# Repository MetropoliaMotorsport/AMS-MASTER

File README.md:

Changes for next year:
Labels on other side
Remove unused connectors
Add connection for temperature measurement of DCDC

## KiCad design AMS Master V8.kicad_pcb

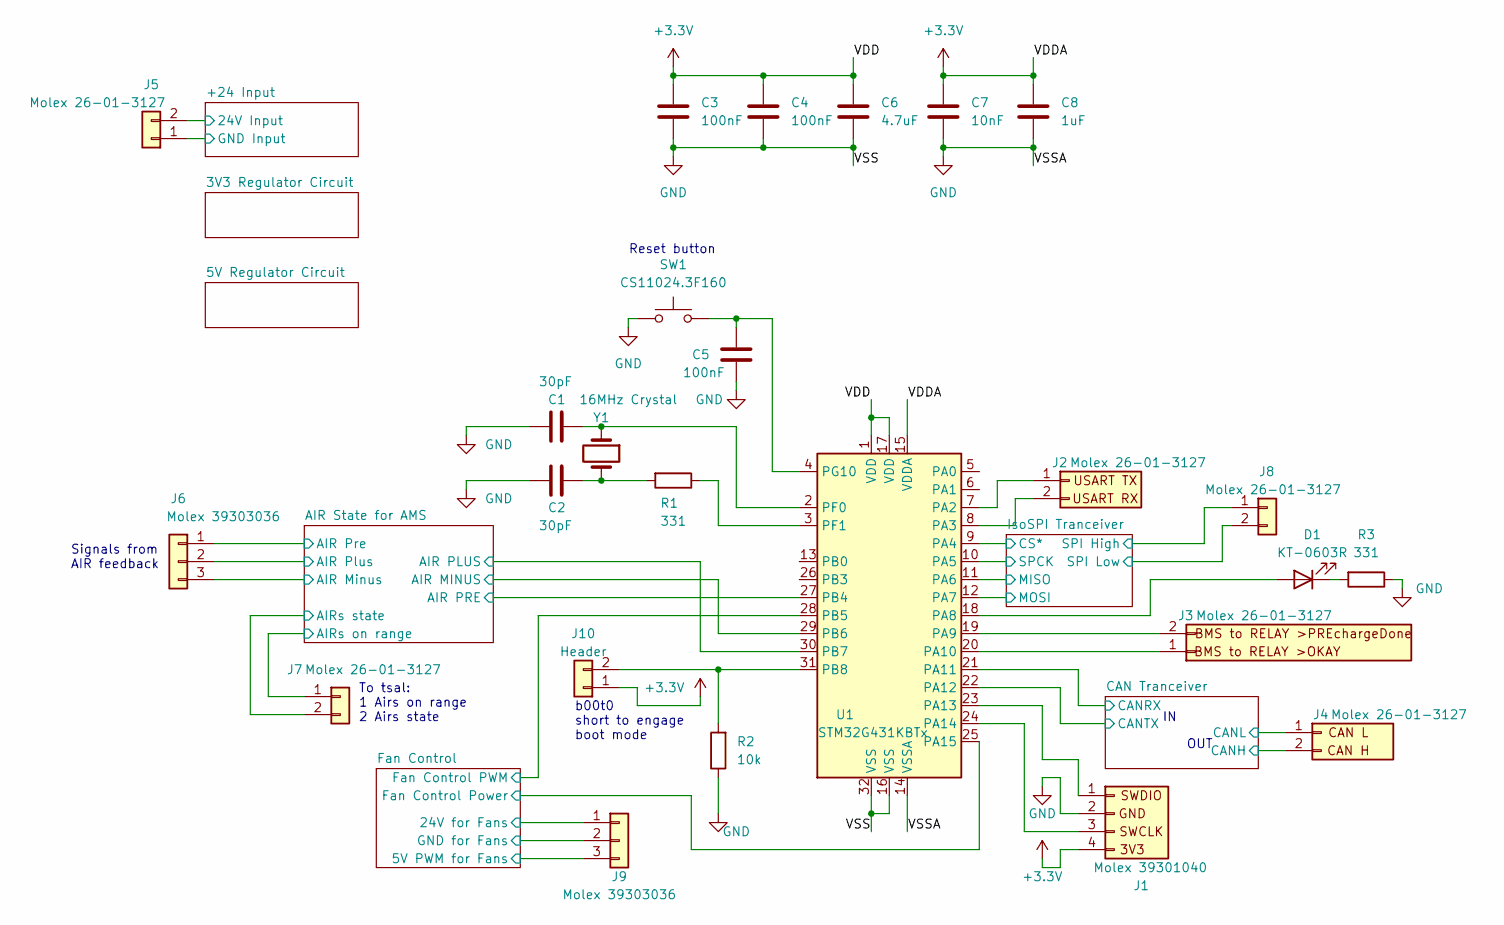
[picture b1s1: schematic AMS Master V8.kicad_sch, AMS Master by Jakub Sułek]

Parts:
C1, C2: 30pF; C_0805_2012Metric_Pad1.18x1.45mm_HandSolder
C3, C4: 100nF; C_0603_1608Metric_Pad1.08x0.95mm_HandSolder
C5: 100nF; C_0805_2012Metric_Pad1.18x1.45mm_HandSolder
C6: 4.7uF; C_0603_1608Metric_Pad1.08x0.95mm_HandSolder
C7: 10nF; C_0603_1608Metric_Pad1.08x0.95mm_HandSolder
C8: 1uF; C_0603_1608Metric_Pad1.08x0.95mm_HandSolder
D1: KT-0603R; LED_0603_1608Metric_Pad1.05x0.95mm_HandSolder
J1: Molex 39301040; Molex_Mini-Fit_Jr_5569-04A2_2x02_P4.20mm_Horizontal
J2, J3, J4, J5, J7, J8: Molex 26-01-3127; Molex_Mini-Fit_Jr_5569-02A2_2x01_P4.20mm_Horizontal
J6, J9: Molex 39303036; Molex_Mini-Fit_Jr_5569-03A4_1x03_P4.20mm_Horizontal
J10: Header; PinHeader_1x02_P2.54mm_Vertical
R1, R3: 331; R_0603_1608Metric_Pad0.98x0.95mm_HandSolder
R2: 10k; R_0805_2012Metric_Pad1.20x1.40mm_HandSolder
SW1: CS11024.3F160; SW_Push_1P1T_NO_6x6mm_H9.5mm
U1: STM32G431KBTx; LQFP-32_7x7mm_P0.8mm
Y1: 16MHz Crystal; Crystal_SMD_HC49-SD

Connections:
+VDC: J5.2; also elsewhere on the board
/AIR State for AMS/AIR MINUS: U1.29 (PB6); also elsewhere on the board
/AIR State for AMS/AIR Minus: J6.3; also elsewhere on the board
/AIR State for AMS/AIR PLUS: U1.30 (PB7); also elsewhere on the board
/AIR State for AMS/AIR PRE: U1.27 (PB4); also elsewhere on the board
/AIR State for AMS/AIR Plus: J6.2; also elsewhere on the board
/AIR State for AMS/AIR Pre: J6.1; also elsewhere on the board
/AIR State for AMS/AIRs on range: J7.1; also elsewhere on the board
/AIR State for AMS/AIRs state: J7.2; also elsewhere on the board
/CAN Tranceiver/CANH: J4.2; also elsewhere on the board
/CAN Tranceiver/CANL: J4.1; also elsewhere on the board
/CAN Tranceiver/CANRX: U1.21 (PA11); also elsewhere on the board
/CAN Tranceiver/CANTX: U1.22 (PA12); also elsewhere on the board
/Fan Control/5V PWM for Fans: J9.3, U1.28 (PB5)
/Fan Control/24V for Fans: J9.1; also elsewhere on the board
/Fan Control/Fan Control Power: U1.25 (PA15); also elsewhere on the board
/IsoSPI Tranceiver/CS*: U1.9 (PA4); also elsewhere on the board
/IsoSPI Tranceiver/MISO: U1.11 (PA6); also elsewhere on the board
/IsoSPI Tranceiver/MOSI: U1.12 (PA7); also elsewhere on the board
/IsoSPI Tranceiver/SPCK: U1.10 (PA5); also elsewhere on the board
/IsoSPI Tranceiver/SPI High: J8.1; also elsewhere on the board
/IsoSPI Tranceiver/SPI Low: J8.2; also elsewhere on the board
unnamed: C2.1, R1.2, Y1.2
unnamed: D1.2 (A), U1.18 (PA8)
unnamed: D1.1 (K), R3.2
unnamed: J1.1, U1.23 (PA13)
unnamed: J1.3, U1.24 (PA14)
unnamed: J2.1, U1.7 (PA2)
unnamed: J2.2, U1.8 (PA3)
unnamed: J3.1, U1.20 (PA10)
unnamed: J3.2, U1.19 (PA9)
unnamed: J10.2, R2.2, U1.31 (PB8)
unnamed: C1.1, U1.2 (PF0), Y1.1
unnamed: R1.1, U1.3 (PF1)
unnamed: C5.1, SW1.2, U1.4 (PG10)

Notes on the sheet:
OUT
Reset button
To tsal: 1 Airs on range 2 Airs state
b00t0 short to engage boot mode
Signals from AIR feedback

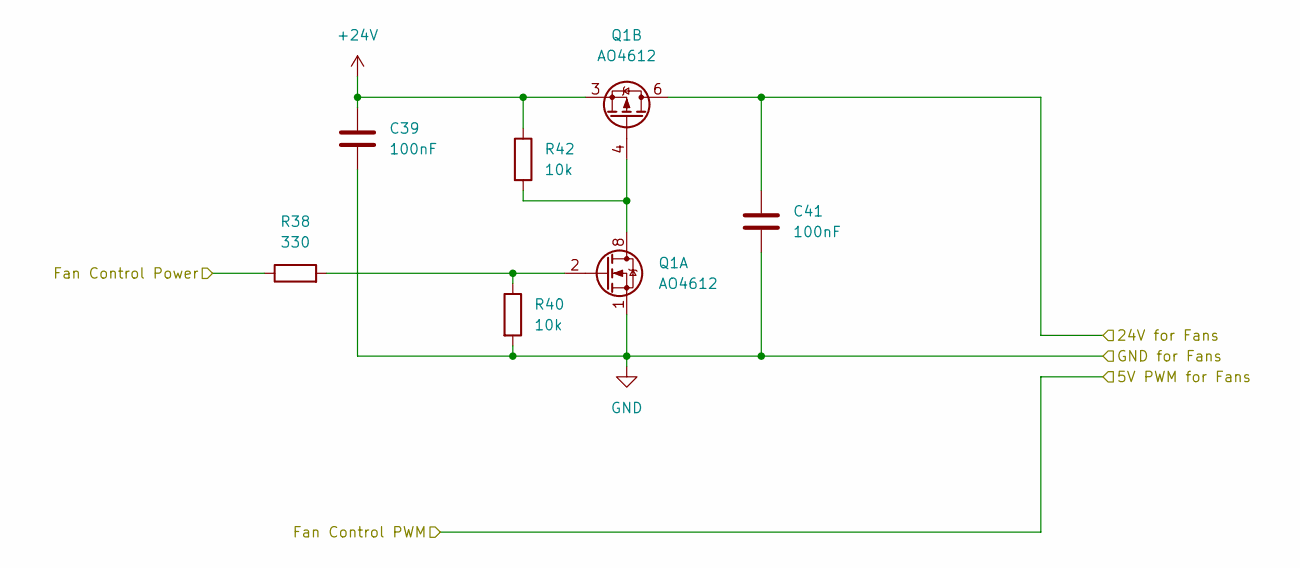
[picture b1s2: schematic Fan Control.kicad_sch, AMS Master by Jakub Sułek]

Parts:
C39, C41: 100nF; C_0805_2012Metric_Pad1.18x1.45mm_HandSolder
Q1: AO4612; SOIC-8_3.9x4.9mm_P1.27mm
R38: 330; R_0805_2012Metric_Pad1.20x1.40mm_HandSolder
R40, R42: 10k; R_0805_2012Metric_Pad1.20x1.40mm_HandSolder

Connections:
+24V: C39.1, Q1.3 (1), R42.1; also elsewhere on the board
/Fan Control/24V for Fans: C41.1, Q1.5 (D), Q1.6 (D); also elsewhere on the board
/Fan Control/Fan Control Power: R38.1; also elsewhere on the board
unnamed: Q1.2 (G), R38.2, R40.1
unnamed: Q1.4 (G), Q1.7 (D), Q1.8 (D), R42.2

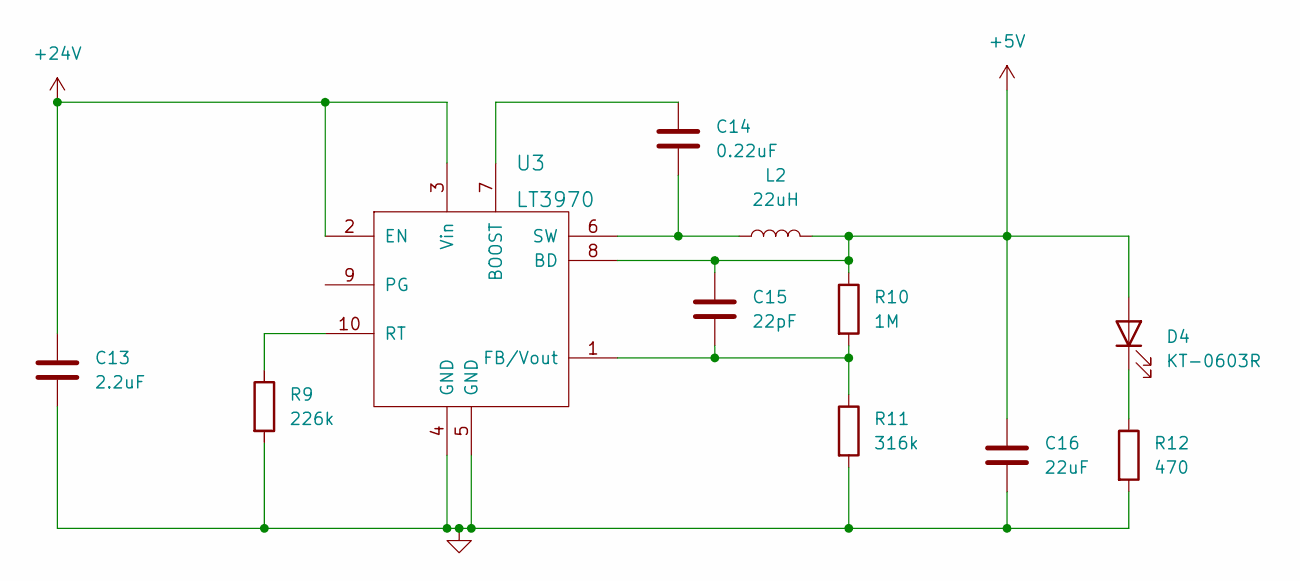
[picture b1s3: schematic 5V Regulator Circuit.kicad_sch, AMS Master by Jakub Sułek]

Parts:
C13: 2.2uF; C_0805_2012Metric_Pad1.18x1.45mm_HandSolder
C14: 0.22uF; C_0805_2012Metric_Pad1.18x1.45mm_HandSolder
C15: 22pF; C_0805_2012Metric_Pad1.18x1.45mm_HandSolder
C16: 22uF; C_0805_2012Metric_Pad1.18x1.45mm_HandSolder
D4: KT-0603R; LED_0603_1608Metric_Pad1.05x0.95mm_HandSolder
L2: 22uH; SLF7045T
R9: 226k; R_0805_2012Metric_Pad1.20x1.40mm_HandSolder
R10: 1M; R_0805_2012Metric_Pad1.20x1.40mm_HandSolder
R11: 316k; R_0805_2012Metric_Pad1.20x1.40mm_HandSolder
R12: 470; R_0805_2012Metric_Pad1.20x1.40mm_HandSolder
U3: LT3970

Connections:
+5V: C15.1, C16.1, D4.2 (A), L2.2, R10.1, U3.8 (BD); also elsewhere on the board
+24V: C13.1, U3.2 (EN), U3.3 (Vin); also elsewhere on the board
unnamed: D4.1 (K), R12.1
unnamed: C14.1, U3.7 (BOOST)
unnamed: C15.2, R10.2, R11.1, U3.1 (FB/Vout)
unnamed: R9.1, U3.10 (RT)
unnamed: C14.2, L2.1, U3.6 (SW)

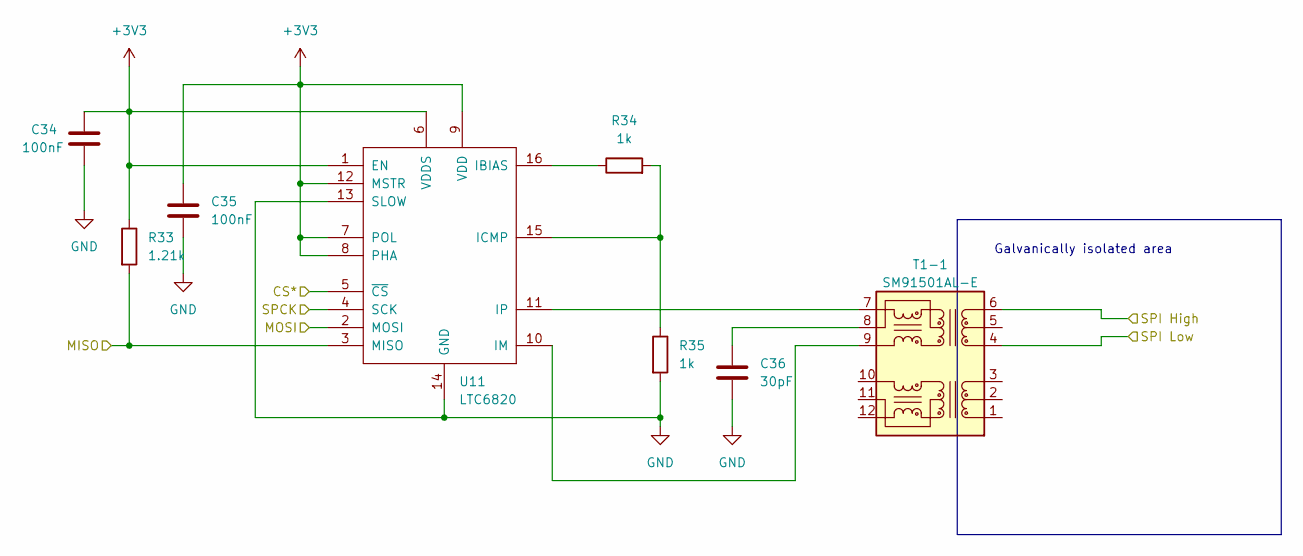
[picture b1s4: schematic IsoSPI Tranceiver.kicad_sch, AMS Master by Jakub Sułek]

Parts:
C34, C35: 100nF; C_0805_2012Metric_Pad1.18x1.45mm_HandSolder
C36: 30pF; C_0805_2012Metric_Pad1.18x1.45mm_HandSolder
R33: 1.21k; R_0805_2012Metric_Pad1.20x1.40mm_HandSolder
R34, R35: 1k; R_0805_2012Metric_Pad1.20x1.40mm_HandSolder
T1-1: SM91501AL-E
U11: LTC6820; ltc6820

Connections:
/IsoSPI Tranceiver/CS*: U11.5 (~CS); also elsewhere on the board
/IsoSPI Tranceiver/MISO: R33.2, U11.3 (MISO); also elsewhere on the board
/IsoSPI Tranceiver/MOSI: U11.2 (MOSI); also elsewhere on the board
/IsoSPI Tranceiver/SPCK: U11.4 (SCK); also elsewhere on the board
/IsoSPI Tranceiver/SPI High: T1-1.6; also elsewhere on the board
/IsoSPI Tranceiver/SPI Low: T1-1.4; also elsewhere on the board
unnamed: C36.1, T1-1.8
unnamed: R34.1, U11.16 (IBIAS)
unnamed: R34.2, R35.1, U11.15 (ICMP)
unnamed: T1-1.9, U11.10 (IM)
unnamed: T1-1.7, U11.11 (IP)

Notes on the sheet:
Galvanically isolated area

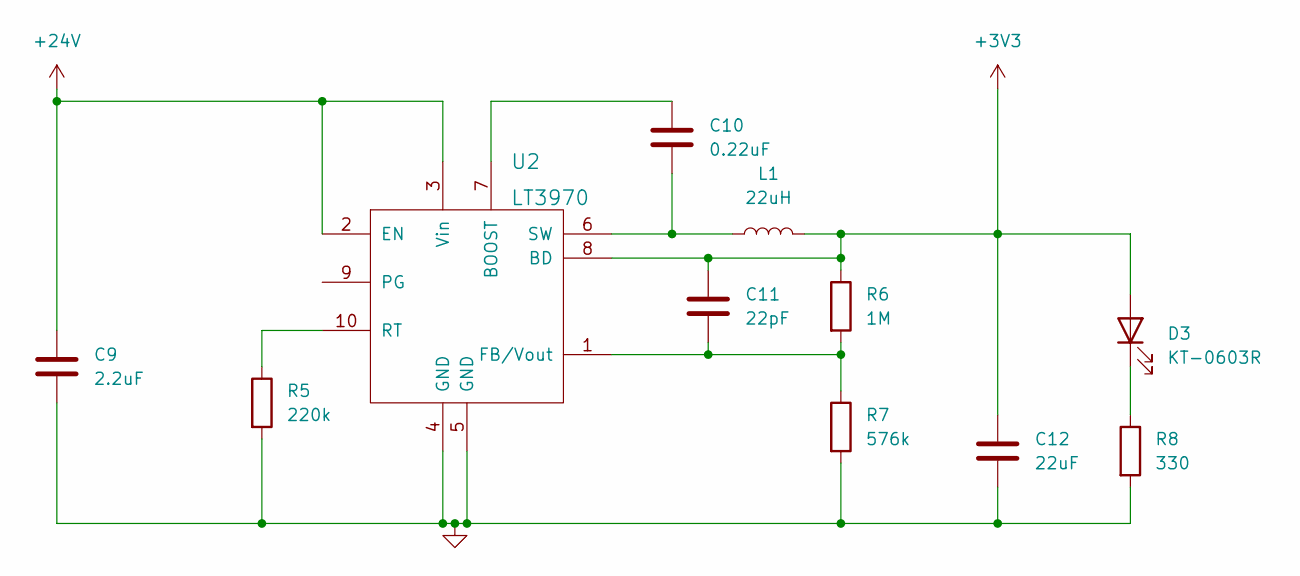
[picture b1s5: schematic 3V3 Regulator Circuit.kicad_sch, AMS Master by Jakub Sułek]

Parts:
C9: 2.2uF; C_0805_2012Metric_Pad1.18x1.45mm_HandSolder
C10: 0.22uF; C_0805_2012Metric_Pad1.18x1.45mm_HandSolder
C11: 22pF; C_0805_2012Metric_Pad1.18x1.45mm_HandSolder
C12: 22uF; C_0805_2012Metric_Pad1.18x1.45mm_HandSolder
D3: KT-0603R; LED_0603_1608Metric_Pad1.05x0.95mm_HandSolder
L1: 22uH; SLF7045T
R5: 220k; R_0805_2012Metric_Pad1.20x1.40mm_HandSolder
R6: 1M; R_0805_2012Metric_Pad1.20x1.40mm_HandSolder
R7: 576k; R_0805_2012Metric_Pad1.20x1.40mm_HandSolder
R8: 330; R_0805_2012Metric_Pad1.20x1.40mm_HandSolder
U2: LT3970

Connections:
+24V: C9.1, U2.2 (EN), U2.3 (Vin); also elsewhere on the board
unnamed: D3.1 (K), R8.1
unnamed: C10.1, U2.7 (BOOST)
unnamed: C11.2, R6.2, R7.1, U2.1 (FB/Vout)
unnamed: R5.1, U2.10 (RT)
unnamed: C10.2, L1.1, U2.6 (SW)

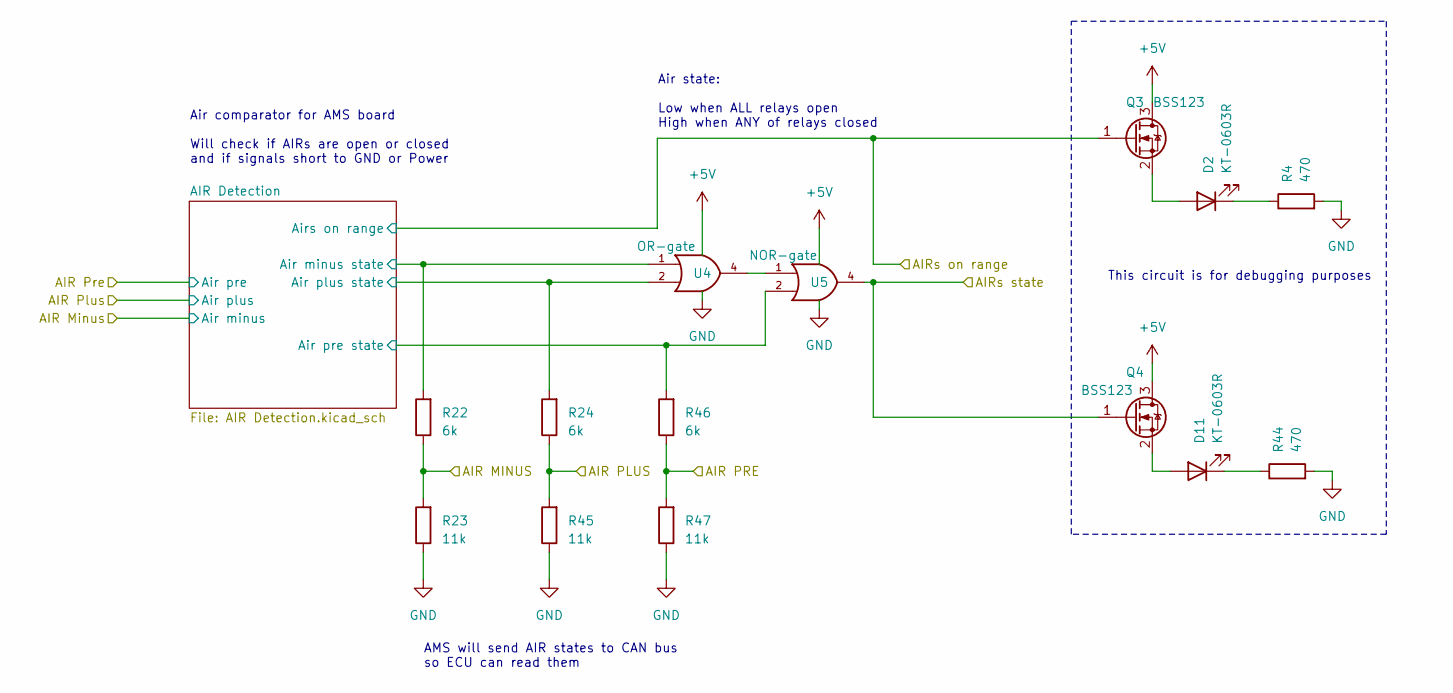
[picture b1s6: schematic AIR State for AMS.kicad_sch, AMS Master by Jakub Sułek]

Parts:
D2, D11: KT-0603R; LED_0603_1608Metric_Pad1.05x0.95mm_HandSolder
Q3, Q4: BSS123; SOT-323_SC-70_Handsoldering
R4, R44: 470; R_0805_2012Metric_Pad1.20x1.40mm_HandSolder
R22, R24, R46: 6k; R_0805_2012Metric_Pad1.20x1.40mm_HandSolder
R23, R45, R47: 11k; R_0805_2012Metric_Pad1.20x1.40mm_HandSolder
U4: OR-gate; SOT-753
U5: NOR-gate; SOT-753

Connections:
+5V: Q3.3 (D), Q4.3 (D), U4.5 (VCC), U5.5 (VCC); also elsewhere on the board
/AIR State for AMS/AIR Detection/Air minus state: R22.2, U4.1; also elsewhere on the board
/AIR State for AMS/AIR Detection/Air plus state: R24.2, U4.2; also elsewhere on the board
/AIR State for AMS/AIR Detection/Air pre state: R46.2, U5.2; also elsewhere on the board
/AIR State for AMS/AIR MINUS: R22.1, R23.2; also elsewhere on the board
/AIR State for AMS/AIR PLUS: R24.1, R45.2; also elsewhere on the board
/AIR State for AMS/AIR PRE: R46.1, R47.2; also elsewhere on the board
/AIR State for AMS/AIRs on range: Q3.1 (G); also elsewhere on the board
/AIR State for AMS/AIRs state: Q4.1 (G), U5.4; also elsewhere on the board
unnamed: D2.2 (A), Q3.2 (S)
unnamed: D2.1 (K), R4.1
unnamed: D11.2 (A), Q4.2 (S)
unnamed: D11.1 (K), R44.1
unnamed: U4.4, U5.1

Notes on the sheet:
This circuit is for debugging purposes
Air state: Low when ALL relays open High when ANY of relays closed
AMS will send AIR states to CAN bus so ECU can read them
Air comparator for AMS board Will check if AIRs are open or closed and if signals short to GND or Power

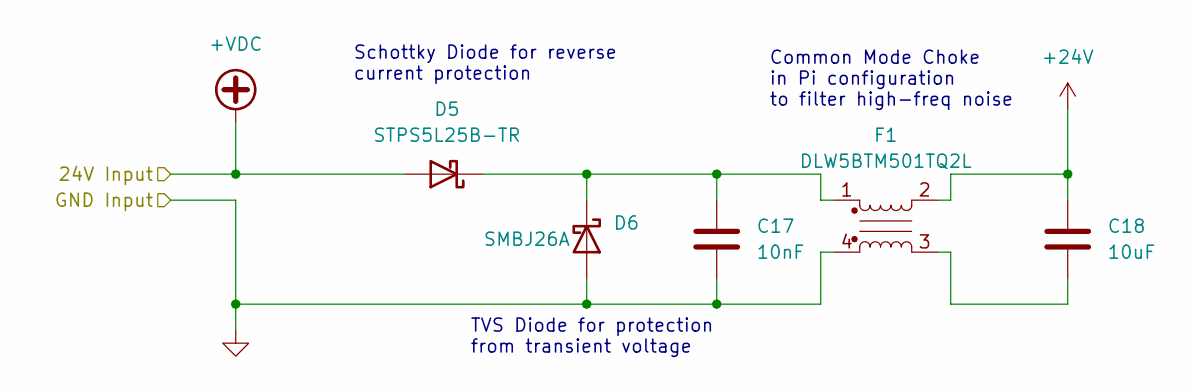
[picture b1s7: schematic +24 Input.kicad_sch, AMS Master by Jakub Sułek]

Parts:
C17: 10nF; C_0805_2012Metric_Pad1.18x1.45mm_HandSolder
C18: 10uF; C_0805_2012Metric_Pad1.18x1.45mm_HandSolder
D5: STPS5L25B-TR; TO-252-2_TabPin1
D6: SMBJ26A; D_SMB
F1: DLW5BTM501TQ2L

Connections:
+24V: C18.1, F1.2; also elsewhere on the board
+VDC: D5.2 (A); also elsewhere on the board
unnamed: C18.2, F1.3
unnamed: C17.1, D5.1 (K), D6.1 (K), F1.1

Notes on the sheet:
Common Mode Choke in Pi configuration to filter high-freq noise
Schottky Diode for reverse current protection
TVS Diode for protection from transient voltage

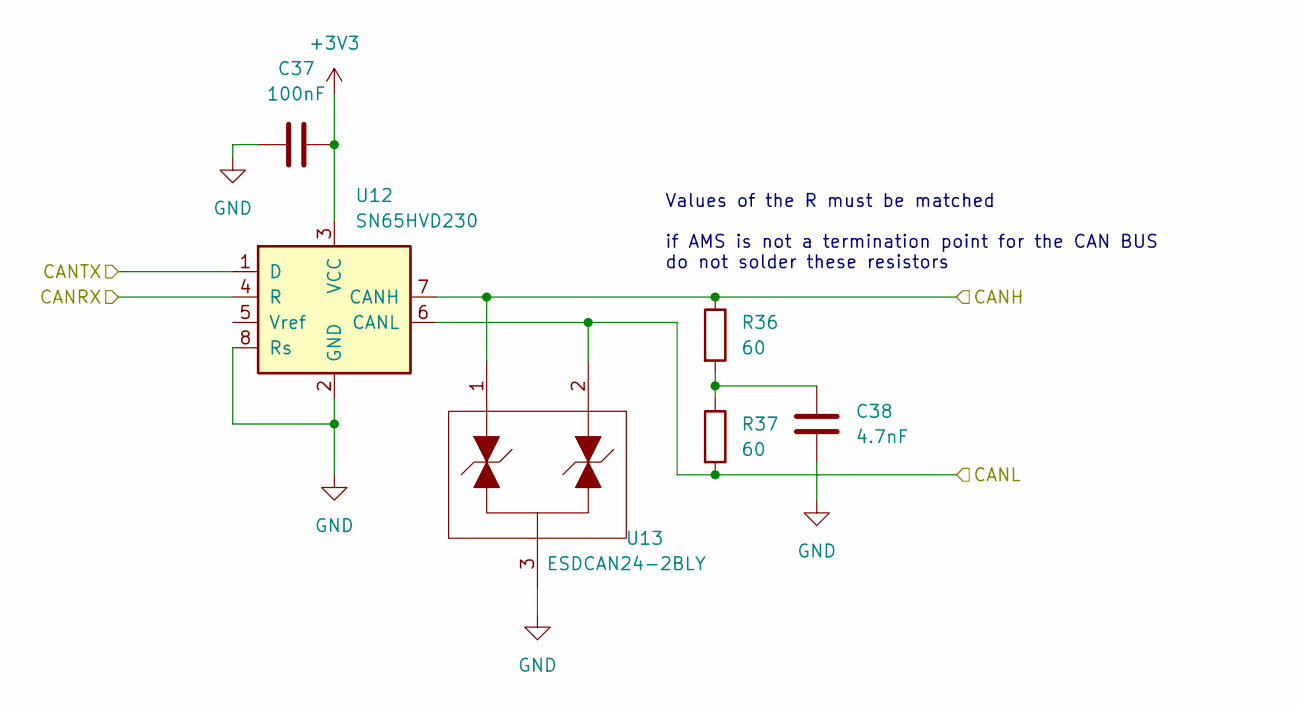
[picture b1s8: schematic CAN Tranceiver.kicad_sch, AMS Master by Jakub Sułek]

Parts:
C37: 100nF; C_0805_2012Metric_Pad1.18x1.45mm_HandSolder
C38: 4.7nF; C_0805_2012Metric_Pad1.18x1.45mm_HandSolder
R36, R37: 60; R_0603_1608Metric_Pad0.98x0.95mm_HandSolder
U12: SN65HVD230; SOIC-8_3.9x4.9mm_P1.27mm
U13: ESDCAN24-2BLY; SOT-23-3

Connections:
/CAN Tranceiver/CANH: R36.1, U12.7 (CANH), U13.1; also elsewhere on the board
/CAN Tranceiver/CANL: R37.2, U12.6 (CANL), U13.2; also elsewhere on the board
/CAN Tranceiver/CANRX: U12.4 (R); also elsewhere on the board
/CAN Tranceiver/CANTX: U12.1 (D); also elsewhere on the board
unnamed: C38.1, R36.2, R37.1

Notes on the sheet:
Values of the R must be matched if AMS is not a termination point for the CAN BUS do not solder these resistors

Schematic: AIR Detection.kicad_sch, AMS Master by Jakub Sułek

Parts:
C19, C20, C21, C23, C24, C25, C26, C27, C28, C29, C30, C31, C32, C33: 100nF; C_0805_2012Metric_Pad1.18x1.45mm_HandSolder
D7, D8, D9, D12: 5.1V; SOD-323
R13, R14, R15: 10K; R_0805_2012Metric_Pad1.20x1.40mm_HandSolder
R16, R17, R18, R19, R20, R21: 33k; R_0805_2012Metric_Pad1.20x1.40mm_HandSolder
R25, R26, R28: 22k; R_0805_2012Metric_Pad1.20x1.40mm_HandSolder
R27: 2.2k; R_0805_2012Metric_Pad1.20x1.40mm_HandSolder
R29: 15k; R_0805_2012Metric_Pad1.20x1.40mm_HandSolder
R30: 9.1k; R_0805_2012Metric_Pad1.20x1.40mm_HandSolder
R31: 11k; R_0805_2012Metric_Pad1.20x1.40mm_HandSolder
R32: 13k; R_0805_2012Metric_Pad1.20x1.40mm_HandSolder
U6, U7, U8, U9, U10: LM293; SOIC-8

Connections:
+24V: C23.1, C24.1, C28.1, C29.1, C30.1, R16.1, R17.1, R18.1, R25.2, R26.2, R27.1, R29.1, R31.1, U6.8 (V+), U7.8 (V+), U8.8 (V+), U9.8 (V+), U10.8 (V+); also elsewhere on the board
/AIR State for AMS/AIR Detection/Air minus state: C26.2, D12.1 (K), R20.1; also elsewhere on the board
/AIR State for AMS/AIR Detection/Air plus state: C25.2, D8.1 (K), R19.1; also elsewhere on the board
/AIR State for AMS/AIR Detection/Air pre state: C27.2, D7.1 (K), R21.1; also elsewhere on the board
/AIR State for AMS/AIR Minus: C20.2, R13.2, U7.2 (-), U7.5 (+), U9.5 (+); also elsewhere on the board
/AIR State for AMS/AIR Plus: C19.2, R14.2, U6.2 (-), U6.5 (+), U9.3 (+); also elsewhere on the board
/AIR State for AMS/AIR Pre: C21.2, R15.2, U8.2 (-), U8.5 (+), U10.3 (+); also elsewhere on the board
/AIR State for AMS/AIRs on range: D9.1 (K), R26.1, U10.7; also elsewhere on the board
unnamed: R16.2, R19.2, U9.1
unnamed: R17.2, R20.2, U9.7
unnamed: R18.2, R21.2, U10.1
unnamed: R25.1, U6.1, U6.7, U7.1, U7.7, U8.1, U8.7, U10.5 (+)
closed: C33.1, R31.2, R32.1, U9.2 (-), U9.6 (-), U10.2 (-)
overrange: C31.1, R27.2, R28.1, U6.3 (+), U7.3 (+), U8.3 (+), U10.6 (-)
underrange: C32.1, R29.2, R30.1, U6.6 (-), U7.6 (-), U8.6 (-)

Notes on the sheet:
Vout 13V
Vout 21.81V
Zener diodes change 24V to 5.1V
Checking if AIRs are open or closed: if yes, the output is pulled up to 24V, if not, the output is being pulled to GND through the comparator
Reference voltages
Vout 9.06V
High if AIRs on range, low if not
Checking if feedbacks from AIRs are within the correct voltage range

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
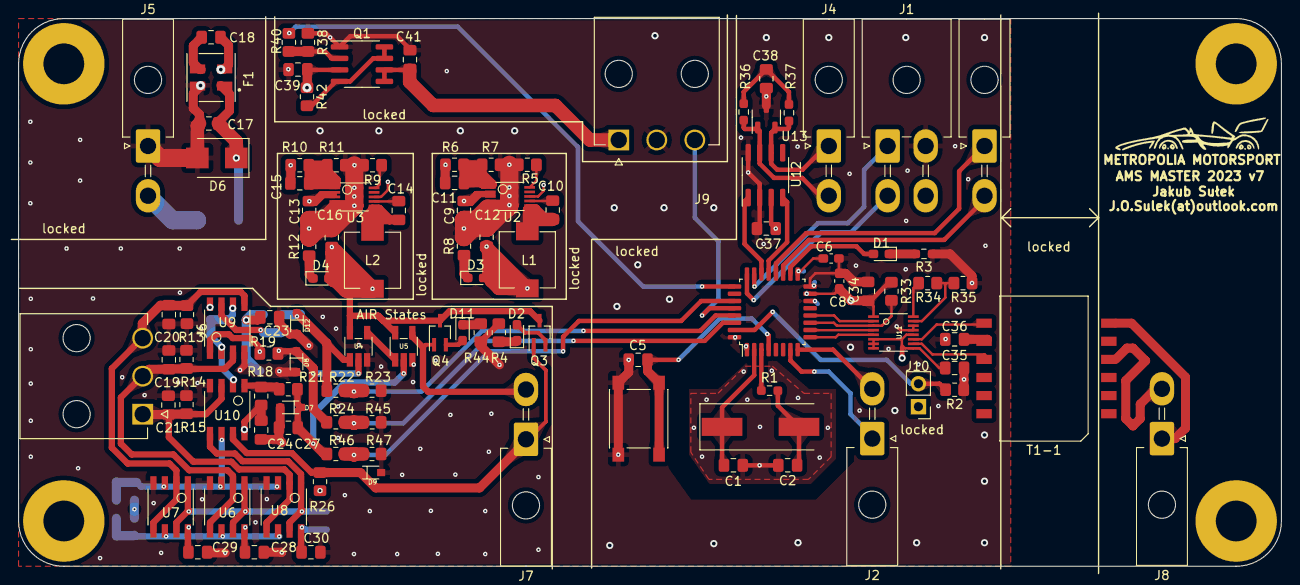
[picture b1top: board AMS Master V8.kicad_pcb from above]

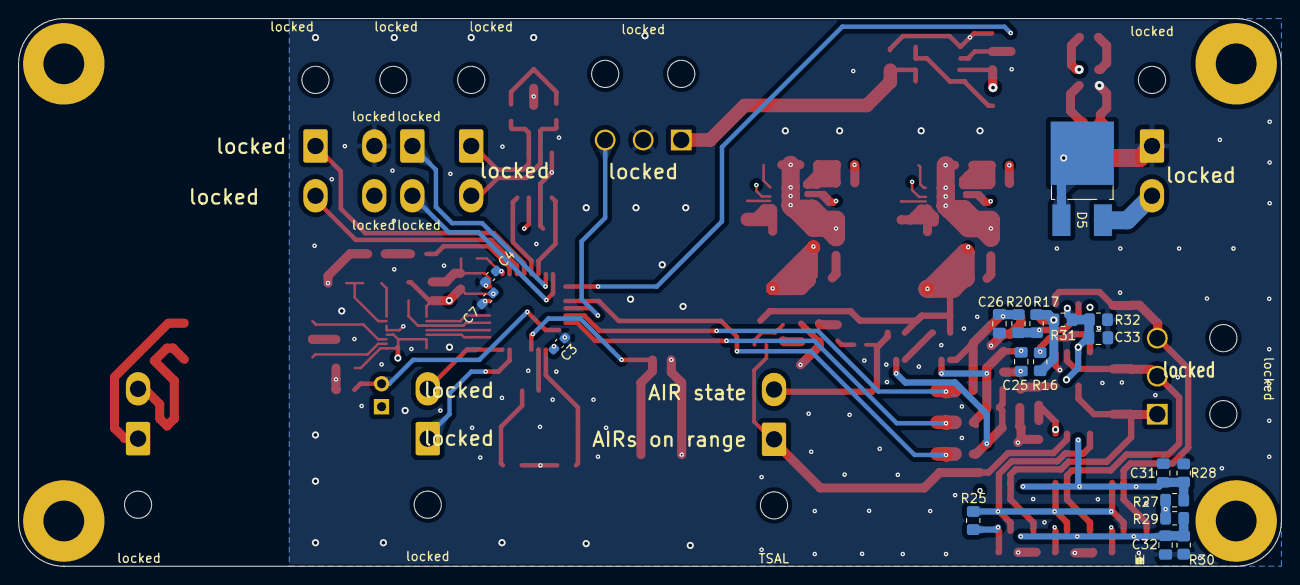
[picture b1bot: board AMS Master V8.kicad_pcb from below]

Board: 4 copper layers, 139.5 x 60.5 mm, 126 parts (19 on the bottom side), 74 nets.

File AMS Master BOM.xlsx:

References | Value | Footprint | Quantity | €/pc | Total price
C5, C19, C20, C21, C23, C24, C25, C26, C27, C28, C29, C30, C31, C32, C33, C34, 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 | 100nF | C_0805_2012Metric_Pad1.18x1.45mm_HandSolder | 22 | 0.04 | 0.88
C1, C2, C36 | 30pF | C_0805_2012Metric_Pad1.18x1.45mm_HandSolder | 3 | 0.31 | 0.92999999999999994
C3, C4 | 100nF | C_0603_1608Metric_Pad1.08x0.95mm_HandSolder | 2 | 0.04 | 0.08
C9, C13 | 2.2uF | C_0805_2012Metric_Pad1.18x1.45mm_HandSolder | 2 | 0.19 | 0.38
C10, C14 | 0.22uF | C_0805_2012Metric_Pad1.18x1.45mm_HandSolder | 2 | 0.1 | 0.2
C11, C15 | 22pF | C_0805_2012Metric_Pad1.18x1.45mm_HandSolder | 2 | 0.15 | 0.3
C12, C16 | 22uF | C_0805_2012Metric_Pad1.18x1.45mm_HandSolder | 2 | 0.22 | 0.44
C6 | 4.7uF | C_0603_1608Metric_Pad1.08x0.95mm_HandSolder | 1 | 0.15 | 0.15
C7 | 10nF | C_0603_1608Metric_Pad1.08x0.95mm_HandSolder | 1 | 0.23 | 0.23
C8 | 1uF | C_0603_1608Metric_Pad1.08x0.95mm_HandSolder | 1 | 0.15 | 0.15
C17 | 10nF | C_0805_2012Metric_Pad1.18x1.45mm_HandSolder | 1 | 0.46 | 0.46
C18 | 10uF | C_0805_2012Metric_Pad1.18x1.45mm_HandSolder | 1 | 0.31 | 0.31
C38 | 4.7nF | C_0805_2012Metric_Pad1.18x1.45mm_HandSolder | 1 | 0.9 | 0.9
R2, R13, R14, R15, R40, R41, R42, R43 | 10k | R_0805_2012Metric_Pad1.20x1.40mm_HandSolder | 8 | 0.02 | 0.16
R16, R17, R18, R19, R20, R21 | 33k | R_0805_2012Metric_Pad1.20x1.40mm_HandSolder | 6 | 0.01 | 0.06
R23, R31, R45, R47 | 11k | R_0805_2012Metric_Pad1.20x1.40mm_HandSolder | 4 | 0.03 | 0.12
R4, R12, R44 | 470 | R_0805_2012Metric_Pad1.20x1.40mm_HandSolder | 3 | 0.03 | 0.09
R8, R38, R39 | 330 | R_0805_2012Metric_Pad1.20x1.40mm_HandSolder | 3 | 0.03 | 0.09
R22, R24, R46 | 6k | R_0805_2012Metric_Pad1.20x1.40mm_HandSolder | 3 | 0.02 | 0.06
R25, R26, R28 | 22k | R_0805_2012Metric_Pad1.20x1.40mm_HandSolder | 3 | 0.03 | 0.09
R1, R3 | 331 | R_0603_1608Metric_Pad0.98x0.95mm_HandSolder | 2 | 0.11 | 0.22
R6, R10 | 1M | R_0805_2012Metric_Pad1.20x1.40mm_HandSolder | 2 | 0.03 | 0.06
R34, R35 | 1k | R_0805_2012Metric_Pad1.20x1.40mm_HandSolder | 2 | 0.28000000000000003 | 0.56000000000000005
R36, R37 | 60 | R_0603_1608Metric_Pad0.98x0.95mm_HandSolder | 2 | 0.26 | 0.52
R5 | 220k | R_0805_2012Metric_Pad1.20x1.40mm_HandSolder | 1 | 0.03 | 0.03
R7 | 576k | R_0805_2012Metric_Pad1.20x1.40mm_HandSolder | 1 | 0.03 | 0.03
R9 | 226k | R_0805_2012Metric_Pad1.20x1.40mm_HandSolder | 1 | 0.03 | 0.03
R11 | 316k | R_0805_2012Metric_Pad1.20x1.40mm_HandSolder | 1 | 0.03 | 0.03
R27 | 2.2k | R_0805_2012Metric_Pad1.20x1.40mm_HandSolder | 1 | 0.28000000000000003 | 0.28000000000000003
R29 | 15k | R_0805_2012Metric_Pad1.20x1.40mm_HandSolder | 1 | 0.03 | 0.03
R30 | 9.1k | R_0805_2012Metric_Pad1.20x1.40mm_HandSolder | 1 | 0.34 | 0.34
R32 | 13k | R_0805_2012Metric_Pad1.20x1.40mm_HandSolder | 1 | 0.03 | 0.03
R33 | 1.21k | R_0805_2012Metric_Pad1.20x1.40mm_HandSolder | 1 | 0.28000000000000003 | 0.28000000000000003
L1, L2 | 22uH | SLF7045T | 2 | 1.04 | 2.08
D1, D2, D3, D4, D11 | KT-0603R | LED_0603_1608Metric_Pad1.05x0.95mm_HandSolder | 5 | 0.13 | 0.65
D7, D8, D9, D12 | 5.1V | SOD-323 | 4 | 0.08 | 0.32
D5 | STPS5L25B-TR | TO-252-2_TabPin1 | 1 | 1.63 | 1.63
D6 | SMBJ26A | DO-214AA | 1 | 0.43 | 0.43
U6, U7, U8, U9, U10 | LM293 | SOIC-8 | 5 | 0.33 | 1.6500000000000001
U2, U3 | LT3970 | LT3970 | 2 | 5.72 | 11.44
U4, U5 | OR-gate | SOT-753 | 2 | 0.19 | 0.38
U1 | STM32G431KBTx | LQFP-32_7x7mm_P0.8mm | 1 | 7.22 | 7.22
U11 | LTC6820 | ltc6820 | 1 | 6.54 | 6.54
U12 | SN65HVD230 | SOIC-8_3.9x4.9mm_P1.27mm | 1 | 3.28 | 3.28
U13 | ESDCAN24-2BLY | SOT-23-3 | 1 | 0.42 | 0.42
Y1 | 16MHz Crystal | Crystal_SMD_HC49-SD | 1 | 0.33 | 0.33
F1 | DLW5BTM501TQ2L | Filter_DLW5BTM501TQ2L | 1 | 1.1599999999999999 | 1.1599999999999999
SW1 | CS11024.3F160 | SW_Push_1P1T_NO_6x6mm_H9.5mm | 1 | 0.25 | 0.25
Q1, Q2 | AO4612 | SOIC-8_3.9x4.9mm_P1.27mm | 2 | 0.73 | 1.46
Q3, Q4 | BSS123 | SOT-323_SC-70_Handsoldering | 2 | 0.27 | 0.54
T1-1 | SM91501AL-E | SM91501AL-E | 1 | 5.08 | 5.08
J2, J3, J4, J5, J7, J8 | Molex 26-01-3127 | Molex_Mini-Fit_Jr_5569-02A2_2x01_P4.20mm_Horizontal | 6 | 0.68 | 4.08
J6, J9 | Molex 39303036 | Molex_Mini-Fit_Jr_5569-03A4_1x03_P4.20mm_Horizontal | 2 | 0.74 | 1.48
J1 | Molex 39301040 | Molex_Mini-Fit_Jr_5569-04A2_2x02_P4.20mm_Horizontal | 1 | 0.57999999999999996 | 0.57999999999999996
PCB |  |  | 1 | 27.11 | 27.11
 |  |  |  |  | 86.63
